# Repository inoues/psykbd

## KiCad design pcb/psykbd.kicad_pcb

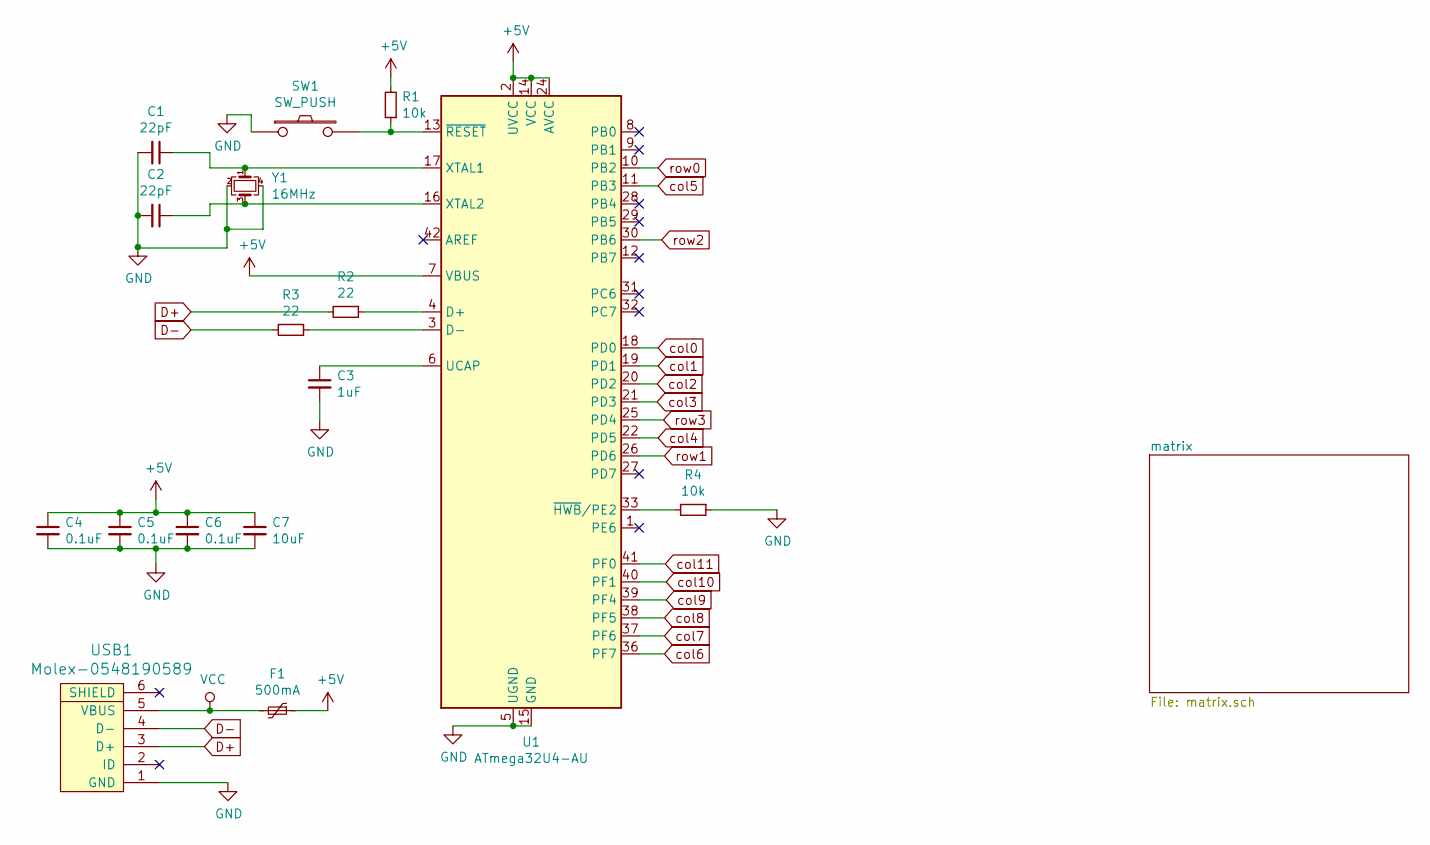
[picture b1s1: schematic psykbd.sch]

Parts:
C1, C2: 22pF; C_0805_2012Metric_Pad1.15x1.40mm_HandSolder
C3: 1uF; C_0805_2012Metric_Pad1.15x1.40mm_HandSolder
C4, C5, C6: 0.1uF; C_0805_2012Metric_Pad1.15x1.40mm_HandSolder
C7: 10uF; C_0805_2012Metric_Pad1.15x1.40mm_HandSolder
F1: 500mA; Fuse_1206_3216Metric_Pad1.42x1.75mm_HandSolder
R1, R4: 10k; R_0805
R2, R3: 22; R_0805
SW1: SW_PUSH; ResetSW_1side
U1: ATmega32U4-AU; TQFP-44_10x10mm_P0.8mm
USB1: Molex-0548190589
Y1: 16MHz; Crystal_SMD_3225-4Pin_3.2x2.5mm_HandSoldering

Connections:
+5V: C4.1, C5.1, C6.1, C7.1, F1.1, R1.2, U1.2 (UVCC), U1.7 (VBUS), U1.14 (VCC), U1.24 (AVCC), U1.34 (VCC), U1.44 (AVCC)
D+: R2.2, USB1.3 (D+)
D-: R3.2, USB1.4 (D-)
GND: C1.2, C2.2, C3.2, C4.2, C5.2, C6.2, C7.2, R4.1, SW1.1, U1.5 (UGND), U1.15 (GND), U1.23 (GND), U1.35 (GND), U1.43 (GND), USB1.1 (GND), Y1.2, Y1.4
unnamed: C1.1, U1.17 (XTAL1), Y1.1
unnamed: C2.1, U1.16 (XTAL2), Y1.3
unnamed: C3.1, U1.6 (UCAP)
unnamed: R1.1, SW1.2, U1.13 (~RESET)
unnamed: R2.1, U1.4 (D+)
unnamed: R3.1, U1.3 (D-)
unnamed: R4.2, U1.33 (~HWB~/PE2)
VCC: F1.2, USB1.5 (VBUS)
col0: U1.18 (PD0); also elsewhere on the board
col1: U1.19 (PD1); also elsewhere on the board
col2: U1.20 (PD2); also elsewhere on the board
col3: U1.21 (PD3); also elsewhere on the board
col4: U1.22 (PD5); also elsewhere on the board
col5: U1.11 (PB3); also elsewhere on the board
col6: U1.36 (PF7); also elsewhere on the board
col7: U1.37 (PF6); also elsewhere on the board
col8: U1.38 (PF5); also elsewhere on the board
col9: U1.39 (PF4); also elsewhere on the board
col10: U1.40 (PF1); also elsewhere on the board
col11: U1.41 (PF0); also elsewhere on the board
row0: U1.10 (PB2); also elsewhere on the board
row1: U1.26 (PD6); also elsewhere on the board
row2: U1.30 (PB6); also elsewhere on the board
row3: U1.25 (PD4); also elsewhere on the board

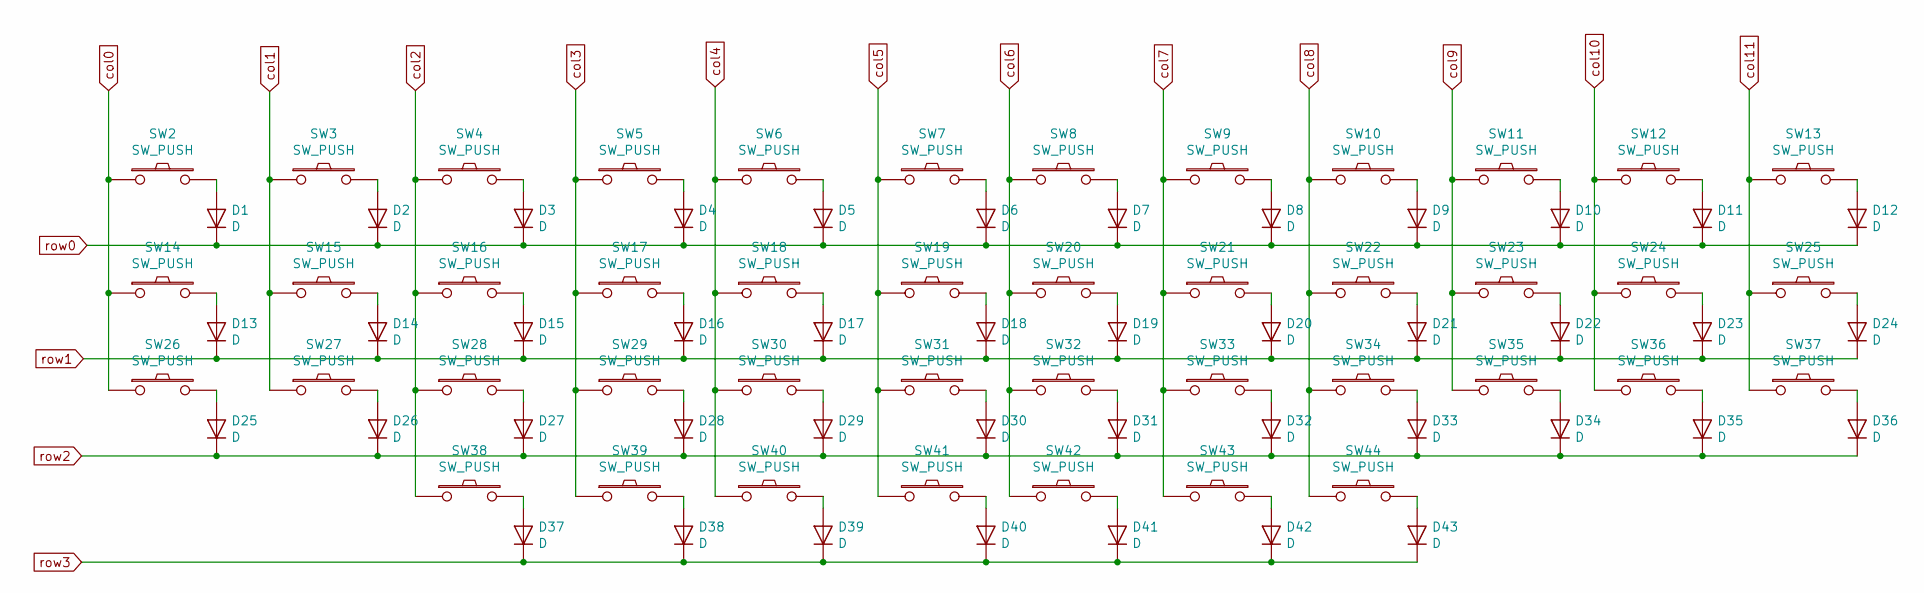
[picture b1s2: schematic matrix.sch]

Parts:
D1, D2, D3, D4, D5, D6, D7, D8, D9, D10, D11, D12, D13, D14, D15, D16, D17, D18, D19, D20, D21, D22, D23, D24, D25, D26, D27, D28, D29, D30, D31, D32, D33, D34, D35, D36, D37, D38, D39, D40, D41, D42, D43: D; D_SOD-123
SW2, SW3, SW4, SW5, SW6, SW7, SW8, SW9, SW10, SW11, SW12, SW13, SW14, SW15, SW16, SW17, SW18, SW19, SW20, SW21, SW22, SW23, SW24, SW25, SW26, SW27, SW28, SW29, SW30, SW31, SW32, SW33, SW34, SW35, SW36, SW37, SW38, SW39, SW41, SW43, SW44: SW_PUSH; MXOnly-1U-Hotswap
SW40, SW42: SW_PUSH; MXOnly-1.5U-Hotswap

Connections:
unnamed: D1.2 (A), SW2.2
unnamed: D2.2 (A), SW3.2
unnamed: D3.2 (A), SW4.2
unnamed: D4.2 (A), SW5.2
unnamed: D5.2 (A), SW6.2
unnamed: D6.2 (A), SW7.2
unnamed: D7.2 (A), SW8.2
unnamed: D8.2 (A), SW9.2
unnamed: D9.2 (A), SW10.2
unnamed: D10.2 (A), SW11.2
unnamed: D11.2 (A), SW12.2
unnamed: D12.2 (A), SW13.2
unnamed: D13.2 (A), SW14.2
unnamed: D14.2 (A), SW15.2
unnamed: D15.2 (A), SW16.2
unnamed: D16.2 (A), SW17.2
unnamed: D17.2 (A), SW18.2
unnamed: D18.2 (A), SW19.2
unnamed: D19.2 (A), SW20.2
unnamed: D20.2 (A), SW21.2
unnamed: D21.2 (A), SW22.2
unnamed: D22.2 (A), SW23.2
unnamed: D23.2 (A), SW24.2
unnamed: D24.2 (A), SW25.2
unnamed: D25.2 (A), SW26.2
unnamed: D26.2 (A), SW27.2
unnamed: D27.2 (A), SW28.2
unnamed: D28.2 (A), SW29.2
unnamed: D29.2 (A), SW30.2
unnamed: D30.2 (A), SW31.2
unnamed: D31.2 (A), SW32.2
unnamed: D32.2 (A), SW33.2
unnamed: D33.2 (A), SW34.2
unnamed: D34.2 (A), SW35.2
unnamed: D35.2 (A), SW36.2
unnamed: D36.2 (A), SW37.2
unnamed: D37.2 (A), SW38.2
unnamed: D38.2 (A), SW39.2
unnamed: D39.2 (A), SW40.2
unnamed: D40.2 (A), SW41.2
unnamed: D41.2 (A), SW42.2
unnamed: D42.2 (A), SW43.2
unnamed: D43.2 (A), SW44.2
col0: SW2.1, SW14.1, SW26.1; also elsewhere on the board
col1: SW3.1, SW15.1, SW27.1; also elsewhere on the board
col2: SW4.1, SW16.1, SW28.1, SW38.1; also elsewhere on the board
col3: SW5.1, SW17.1, SW29.1, SW39.1; also elsewhere on the board
col4: SW6.1, SW18.1, SW30.1, SW40.1; also elsewhere on the board
col5: SW7.1, SW19.1, SW31.1, SW41.1; also elsewhere on the board
col6: SW8.1, SW20.1, SW32.1, SW42.1; also elsewhere on the board
col7: SW9.1, SW21.1, SW33.1, SW43.1; also elsewhere on the board
col8: SW10.1, SW22.1, SW34.1, SW44.1; also elsewhere on the board
col9: SW11.1, SW23.1, SW35.1; also elsewhere on the board
col10: SW12.1, SW24.1, SW36.1; also elsewhere on the board
col11: SW13.1, SW25.1, SW37.1; also elsewhere on the board
row0: D1.1 (K), D2.1 (K), D3.1 (K), D4.1 (K), D5.1 (K), D6.1 (K), D7.1 (K), D8.1 (K), D9.1 (K), D10.1 (K), D11.1 (K), D12.1 (K); also elsewhere on the board
row1: D13.1 (K), D14.1 (K), D15.1 (K), D16.1 (K), D17.1 (K), D18.1 (K), D19.1 (K), D20.1 (K), D21.1 (K), D22.1 (K), D23.1 (K), D24.1 (K); also elsewhere on the board
row2: D25.1 (K), D26.1 (K), D27.1 (K), D28.1 (K), D29.1 (K), D30.1 (K), D31.1 (K), D32.1 (K), D33.1 (K), D34.1 (K), D35.1 (K), D36.1 (K); also elsewhere on the board
row3: D37.1 (K), D38.1 (K), D39.1 (K), D40.1 (K), D41.1 (K), D42.1 (K), D43.1 (K); also elsewhere on the board

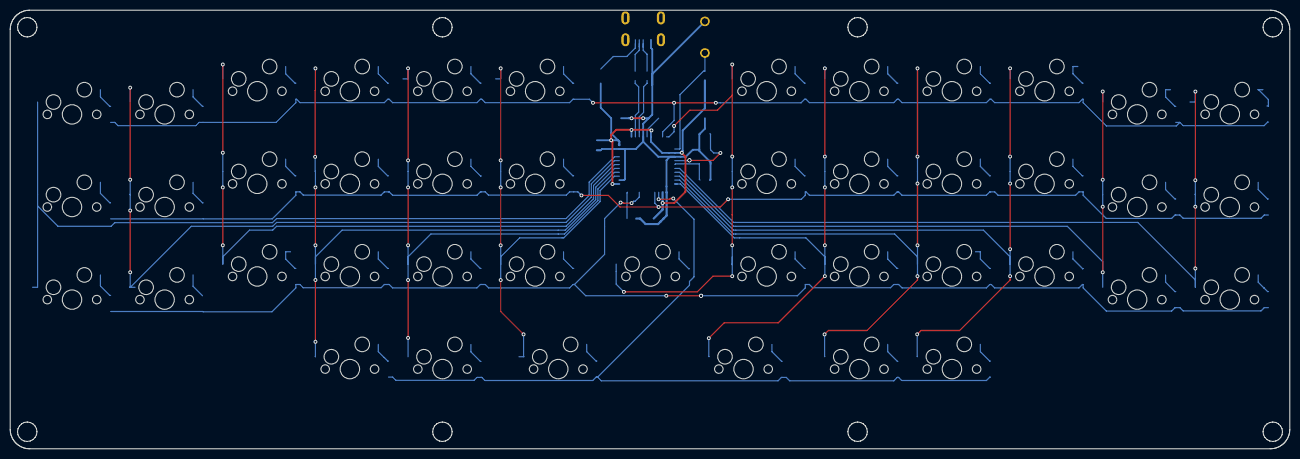
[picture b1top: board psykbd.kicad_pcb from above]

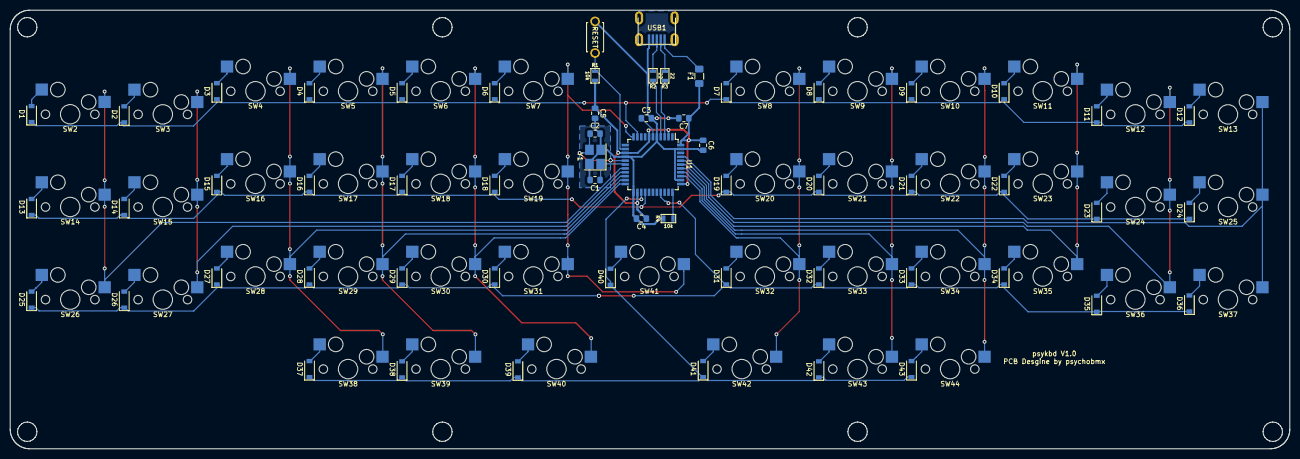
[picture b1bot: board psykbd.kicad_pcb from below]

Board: 2 copper layers, 263.2 x 90.2 mm, 102 parts (59 on the bottom side), 71 nets.

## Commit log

2020-01-02 create Kicad project
2020-01-02 add pretty submoduels
2020-01-02 add footprint lib
2020-01-02 add plate
2020-01-02 MCU schematic
2020-01-02 add USB micro b
2020-01-04 Assigning Footprints
2020-01-05 Routing
2020-01-06 chenge mcu position
2020-01-09 re Routing
2020-01-11 before check
2020-01-12 fix dcr check error and chgenge switch footprint
2020-01-12 add psychobmx logo
